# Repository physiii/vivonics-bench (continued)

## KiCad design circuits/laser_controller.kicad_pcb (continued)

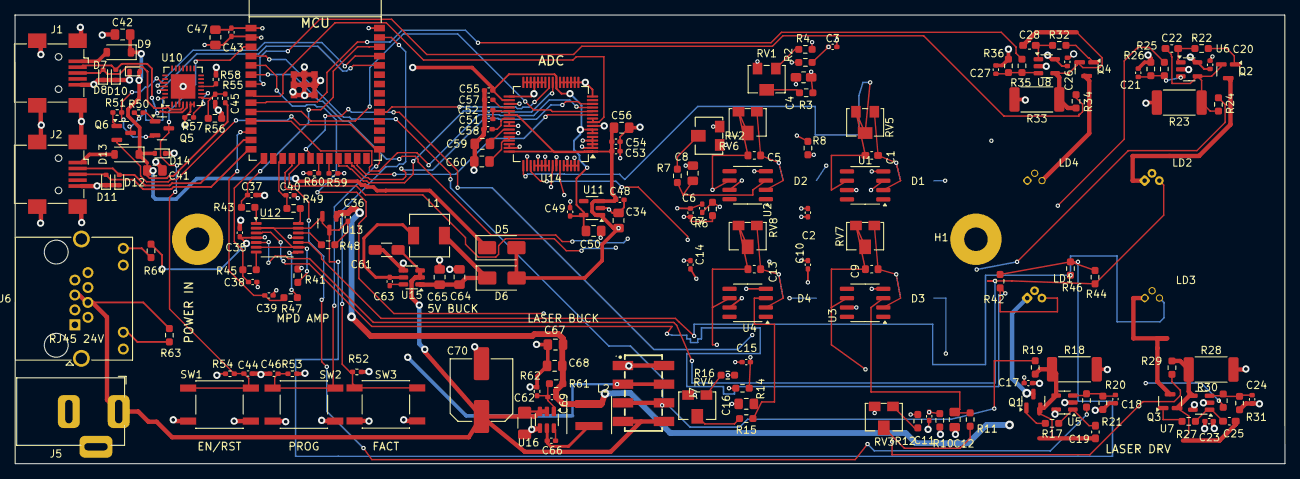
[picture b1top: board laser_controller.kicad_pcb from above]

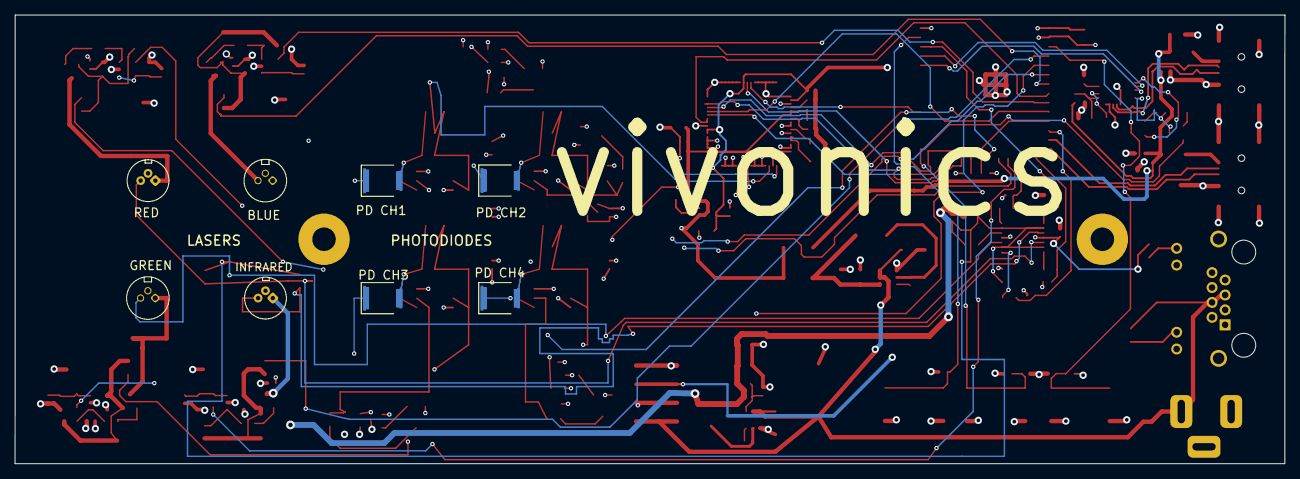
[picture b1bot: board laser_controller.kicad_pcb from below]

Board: 4 copper layers, 173.0 x 61.1 mm, 181 parts (8 on the bottom side), 110 nets.

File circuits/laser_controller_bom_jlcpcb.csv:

Comment,Designator,Footprint,LCSC
"240R MPD sense","R42,R44,R46,R48","Resistor_SMD:R_0603_1608Metric_Pad0.98x0.95mm_HandSolder","C103446"
"10pF C0G","C1,C5,C9,C13,C19,C22,C25,C28","Capacitor_SMD:C_0603_1608Metric_Pad1.08x0.95mm_HandSolder","C106245"
"RF 2M","RV5,RV6,RV7,RV8","Potentiometer_SMD:Potentiometer_Bourns_3224W_Vertical","C116323"
"SW_PUSH","SW1,SW2,SW3","Button_Switch_SMD:SW_SPST_PTS645","C127509"
"100pF FF","C69","Capacitor_SMD:C_0402_1005Metric_Pad0.74x0.62mm_HandSolder","C1546"
"10K","R59,R52,R58,R60,R53,R50,R51,R54","Resistor_SMD:R_0402_1005Metric_Pad0.72x0.64mm_HandSolder","C191123"
"C192300","J7","Open_Automation:PinHeader_2x04_P2.54mm_SMD_Vertical_C192300","C192300"
"24V DC IN","J5","Open_Automation:BarrelJack_OD5.5_ID2.5","C194407"
"OPA380AID","U1,U2,U3,U4","Package_SO:SOIC-8_3.9x4.9mm_P1.27mm","C201677"
"INA4180A1","U12","Package_SO:TSSOP-14_4.4x5mm_P0.65mm","C2057528"
"AP63205WU-7 5V BUCK","U15","Package_TO_SOT_SMD:TSOT-23-6","C2071056"
"AP63200WU-7 9.3V BUCK","U16","Package_TO_SOT_SMD:TSOT-23-6","C2071868"
"AO3400A","Q1,Q2,Q3,Q4","Package_TO_SOT_SMD:SOT-23","C20917"
"1.3k LIMIT","R21","Resistor_SMD:R_0603_1608Metric_Pad0.98x0.95mm_HandSolder","C22767"
"2.49k MPD bias","R41","Resistor_SMD:R_0603_1608Metric_Pad0.98x0.95mm_HandSolder","C22908"
"47.5K","R56","Resistor_SMD:R_0603_1608Metric_Pad0.98x0.95mm_HandSolder","C23061"
"4.7k LIMIT","R36","Resistor_SMD:R_0603_1608Metric_Pad0.98x0.95mm_HandSolder","C23162"
"750R LIMIT","R26","Resistor_SMD:R_0603_1608Metric_Pad0.98x0.95mm_HandSolder","C23241"
"SS14","D5,D6","Diode_SMD:D_SMA","C2480"
"SFH2201","D1,D2,D3,D4","OptoDevice:Osram_SFH2201","C2900216"
"1k","R2,R6,R10,R14,R17,R19,R22,R24,R27,R29,R32,R34","Resistor_SMD:R_0603_1608Metric_Pad0.98x0.95mm_HandSolder","C2907002"
"1k ADC","R43,R45,R47,R49","Resistor_SMD:R_0603_1608Metric_Pad0.98x0.95mm_HandSolder","C2907002"
"ESP32-S3-WROOM-1","U9","Espressif:ESP32-S3-WROOM-1","C2913199"
"22.1K","R55","Resistor_SMD:R_0402_1005Metric_Pad0.72x0.64mm_HandSolder","C2929993"
"22.1K FB","R62","Resistor_SMD:R_0402_1005Metric_Pad0.72x0.64mm_HandSolder","C2929993"
"237k FB","R61","Resistor_SMD:R_0603_1608Metric_Pad0.98x0.95mm_HandSolder","C2998117"
"10uF","C4,C8,C12,C16,C50","Capacitor_SMD:C_0805_2012Metric_Pad1.18x1.45mm_HandSolder","C318691"
"10uF +5V bulk","C34","Capacitor_SMD:C_0805_2012Metric_Pad1.18x1.45mm_HandSolder","C318691"
"10uF ADC AVCC","C56","Capacitor_SMD:C_0805_2012Metric_Pad1.18x1.45mm_HandSolder","C318691"
"10uF ADC REF","C59","Capacitor_SMD:C_0805_2012Metric_Pad1.18x1.45mm_HandSolder","C318691"
"10uF ADC REFCAP","C60","Capacitor_SMD:C_0805_2012Metric_Pad1.18x1.45mm_HandSolder","C318691"
"C_10uF","C41,C47,C42","Capacitor_SMD:C_0805_2012Metric_Pad1.18x1.45mm_HandSolder","C318691"
"CONN_RJ45","J6","Connector_RJ:RJ45_Amphenol_RJHSE538X","C386757"
"Q_L8550HQLT1G","Q6","Package_TO_SOT_SMD:SOT-23","C39282"
"TLV9001","U5,U6,U7,U8","Package_TO_SOT_SMD:SOT-23-5","C398363"
"4.7uH","L1","Open_Automation:L_5.4x5.3_H3","C408410"
"3k LIMIT","R31","Resistor_SMD:R_0603_1608Metric_Pad0.98x0.95mm_HandSolder","C4211"
"22uF 5V buck","C64,C65","Capacitor_SMD:C_0805_2012Metric_Pad1.18x1.45mm_HandSolder","C45783"
"22uF laser buck","C67,C68","Capacitor_SMD:C_0805_2012Metric_Pad1.18x1.45mm_HandSolder","C45783"
"USB_MINI_B","J2,J1","Connector_USB:USB_Mini-B_Wuerth_65100516121_Horizontal","C46391"
"Q_L8050QLT1G","Q5","Package_TO_SOT_SMD:SOT-23","C49581"
"AP2112K-3.3","U11","Package_TO_SOT_SMD:SOT-23-5","C51118"
"10R 2W","R18,R23,R28,R33","Resistor_SMD:R_2512_6332Metric_Pad1.40x3.35mm_HandSolder","C5123624"
"AD7606BSTZ-4","U14","Package_QFP:LQFP-64_10x10mm_P0.5mm","C51512"
"ESD_5V","D7,D14,D9,D11,D12,D8","Diode_SMD:D_SOD-523","C5199850"
"LM4040C50 5V","U13","Package_TO_SOT_SMD:SOT-23","C69316"
"1uF","C3,C7,C11,C15,C18,C21,C24,C27,C48,C46,C44,C45","Capacitor_SMD:C_0402_1005Metric_Pad0.74x0.62mm_HandSolder","C7472946"
"1uF ADC REGCAP","C57,C58","Capacitor_SMD:C_0402_1005Metric_Pad0.74x0.62mm_HandSolder","C7472946"
"VBIAS 10k","RV1,RV2,RV3,RV4","Potentiometer_SMD:Potentiometer_Bourns_3224W_Vertical","C81348"
"D_1N5819HW","D13,D10","Diode_SMD:D_SOD-123","C82544"
"100nF","C2,C6,C10,C14,C17,C20,C23,C26,C49,C35,C43","Capacitor_SMD:C_0402_1005Metric_Pad0.74x0.62mm_HandSolder","C83056"
"100nF ADC AVCC","C51,C52,C53,C54","Capacitor_SMD:C_0402_1005Metric_Pad0.74x0.62mm_HandSolder","C83056"
"100nF ADC VDRIVE","C55","Capacitor_SMD:C_0402_1005Metric_Pad0.74x0.62mm_HandSolder","C83056"
"100nF BST","C63,C66","Capacitor_SMD:C_0402_1005Metric_Pad0.74x0.62mm_HandSolder","C83056"
"100nF MPD ADC","C37,C38,C39,C40","Capacitor_SMD:C_0402_1005Metric_Pad0.74x0.62mm_HandSolder","C83056"
"100nF MPD bias","C36","Capacitor_SMD:C_0402_1005Metric_Pad0.74x0.62mm_HandSolder","C83056"
"10K","R63,R64","Resistor_SMD:R_0603_1608Metric_Pad0.98x0.95mm_HandSolder","C844918"
"10k","R4,R3,R8,R7,R12,R11,R16,R15,R20,R25,R30,R35","Resistor_SMD:R_0603_1608Metric_Pad0.98x0.95mm_HandSolder","C844918"
"1K","R57","Resistor_SMD:R_0402_1005Metric_Pad0.72x0.64mm_HandSolder","C852624"
"10uF 50V","C61,C62","Capacitor_SMD:C_1206_3216Metric_Pad1.33x1.80mm_HandSolder","C89632"
"CP2102N-Axx-xQFN28","U10","Package_DFN_QFN:QFN-28-1EP_5x5mm_P0.5mm_EP3.35x3.35mm","C964632"
"22uF 100V","C70","Capacitor_SMD:C_Elec_8x10.2","C970665"
"10uH","L2","Open_Automation:L_4x4","C98364"

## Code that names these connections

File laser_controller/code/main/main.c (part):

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    GPIO_PWM_GREEN = 12,
    GPIO_PWM_BLUE = 16,
    GPIO_ADC_CONVST = 15,
    GPIO_ADC_SCLK = 17,
    GPIO_ADC_CS = 18,
    GPIO_ADC_DOUTA = 21,
    GPIO_ADC_BUSY = 47,
    GPIO_ADC_RESET = 48,
};

static const char *TAG = "laser_controller";
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    LEDC_CHANNEL_3,
};
static const adc_channel_t TELEMETRY_CHANNELS[TELEMETRY_CHANNEL_COUNT] = {
    ADC_CHANNEL_3, /* GPIO4: ISENSE1 */
    ADC_CHANNEL_4, /* GPIO5: ISENSE2 */
    ADC_CHANNEL_5, /* GPIO6: ISENSE3 */
    ADC_CHANNEL_6, /* GPIO7: ISENSE4 */
    ADC_CHANNEL_1, /* GPIO2: MPD1 */
    ADC_CHANNEL_2, /* GPIO3: MPD2 */
    ADC_CHANNEL_7, /* GPIO8: MPD3 */
    ADC_CHANNEL_8, /* GPIO9: MPD4/spare */
};
static const gpio_num_t TELEMETRY_GPIOS[TELEMETRY_CHANNEL_COUNT] = {
    GPIO_NUM_4, /* ISENSE1 */
    GPIO_NUM_5, /* ISENSE2 */
    GPIO_NUM_6, /* ISENSE3 */
    GPIO_NUM_7, /* ISENSE4 */
    GPIO_NUM_2, /* MPD1 */
    GPIO_NUM_3, /* MPD2 */
    GPIO_NUM_8, /* MPD3 */
    GPIO_NUM_9, /* MPD4/spare */
};
static const char *const TELEMETRY_SIGNAL_NAMES[TELEMETRY_CHANNEL_COUNT] = {
    "ISENSE1",
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    force_all_lasers_off();

    const gpio_config_t adc_output_config = {
        .pin_bit_mask = (1ULL << GPIO_ADC_CONVST) | (1ULL << GPIO_ADC_RESET),
        .mode = GPIO_MODE_OUTPUT,
        .pull_up_en = GPIO_PULLUP_DISABLE,
        .pull_down_en = GPIO_PULLDOWN_ENABLE,
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        return error;
    }
    gpio_set_level(GPIO_ADC_CONVST, 0);
    gpio_set_level(GPIO_ADC_RESET, 0);

    const gpio_config_t busy_config = {
        .pin_bit_mask = 1ULL << GPIO_ADC_BUSY,
        .mode = GPIO_MODE_INPUT,
        .pull_up_en = GPIO_PULLUP_DISABLE,
        .pull_down_en = GPIO_PULLDOWN_DISABLE,
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    if (error != ESP_OK) {
        return error;
    }
    return gpio_isr_handler_add(GPIO_ADC_BUSY, adc_busy_rise_isr, NULL);
}

#if CONFIG_LC_ENABLE_LASER_PULSE_TEST
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    const spi_bus_config_t bus_config = {
        .mosi_io_num = -1,
        .miso_io_num = GPIO_ADC_DOUTA,
        .sclk_io_num = GPIO_ADC_SCLK,
        .quadwp_io_num = -1,
        .quadhd_io_num = -1,
        .max_transfer_sz = AD7606_DOUTA_FRAME_BYTES,
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        .dummy_bits = 0,
        .mode = 1,
        .clock_speed_hz = CONFIG_LC_AD7606_SCLK_HZ,
        .spics_io_num = GPIO_ADC_CS,
        .queue_size = 1,
        .flags = SPI_DEVICE_HALFDUPLEX | SPI_DEVICE_NO_DUMMY,
    };
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
static void reset_adc(void)
{
    const int busy_before = gpio_get_level(GPIO_ADC_BUSY);
    gpio_set_level(GPIO_ADC_RESET, 1);
    esp_rom_delay_us(10);
    const int busy_during_reset = gpio_get_level(GPIO_ADC_BUSY);
    gpio_set_level(GPIO_ADC_RESET, 0);
    esp_rom_delay_us(100);
    ESP_LOGI(
        TAG,
        "ADC_RESET_DIAG busy_before=%d busy_during=%d busy_after=%d",
        busy_before,
        busy_during_reset,
        gpio_get_level(GPIO_ADC_BUSY)
    );
}

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
static bool wait_for_adc_busy_rise(uint32_t timeout_us)
{
    if (adc_busy_rise_latched || gpio_get_level(GPIO_ADC_BUSY) == 1) {
        return true;
    }
    const int64_t deadline = esp_timer_get_time() + timeout_us;
    while (esp_timer_get_time() <= deadline) {
        if (adc_busy_rise_latched || gpio_get_level(GPIO_ADC_BUSY) == 1) {
            return true;
        }
    }
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{
    uint8_t raw[AD7606_DOUTA_FRAME_BYTES] = {0};

    const int busy_before = gpio_get_level(GPIO_ADC_BUSY);
    gpio_set_level(GPIO_ADC_CONVST, 0);
    esp_rom_delay_us(1);
    const int busy_while_convst_low = gpio_get_level(GPIO_ADC_BUSY);
    adc_busy_rise_latched = false;
    gpio_set_level(GPIO_ADC_CONVST, 1);
    const int busy_immediate = gpio_get_level(GPIO_ADC_BUSY);

    const int64_t rise_wait_started_us = esp_timer_get_time();
    if (busy_immediate != 1 &&
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            busy_while_convst_low,
            busy_immediate,
            adc_busy_rise_latched,
            gpio_get_level(GPIO_ADC_BUSY),
            esp_timer_get_time() - rise_wait_started_us
        );
        return LASER_FAULT_ADC_BUSY_RISE_TIMEOUT;
    }
    const int64_t busy_rise_us = esp_timer_get_time() - rise_wait_started_us;
    const int64_t fall_wait_started_us = esp_timer_get_time();
    if (!wait_for_gpio_level(GPIO_ADC_BUSY, 0, CONFIG_LC_AD7606_BUSY_TIMEOUT_US)) {
        ESP_LOGE(
            TAG,
            "ADC_BUSY_FALL_TIMEOUT busy_rise_us=%" PRId64 " busy_after=%d "
            "elapsed_us=%" PRId64,
            busy_rise_us,
            gpio_get_level(GPIO_ADC_BUSY),
            esp_timer_get_time() - fall_wait_started_us
        );
        return LASER_FAULT_ADC_BUSY_FALL_TIMEOUT;
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
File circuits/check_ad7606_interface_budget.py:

#!/usr/bin/env python3
"""AD7606-4 hardware strap and ESP32 serial-read budget check.

This is a firmware-interface contract for the current bench board. It proves
the schematic is wired for the intended AD7606-4 serial mode and that the
default firmware timing target has margin against the datasheet timing path.
It does not prove analog accuracy, final PCB layout, or working firmware.
"""
from __future__ import annotations

import os
import sys
from pathlib import Path

from check_laser_controller_netlist import parse_components, parse_netlist


ADC_REF = "U14"
ESP32_REF = "U9"
ADC_BITS = 16
ADC_CHANNELS = 4
DOUT_LINES = 2
INPUT_SPAN_V = 10.0  # +/-5 V range strap.
INPUT_LSB_UV = INPUT_SPAN_V / (2**ADC_BITS) * 1_000_000
DEFAULT_SPI_MHZ = 10.0
DEFAULT_TARGET_KSPS = 100.0
AD7606_4_NO_OS_CONV_US = 2.0
RESET_HIGH_MIN_NS = 50.0
RESET_TO_CONVST_MIN_NS = 25.0
CONVST_LOW_MIN_NS = 25.0
CONVST_HIGH_MIN_NS = 25.0
BUSY_TO_CS_MIN_NS = 0.0
READ_DURING_BUSY_T6_GUARD_NS = 25.0
DATASHEET_NO_OS_MAX_KSPS = 200.0
CONSERVATIVE_SPI_MAX_MHZ = 10.0


def env_float(name: str, default: float) -> float:
    raw = os.environ.get(name)
    if raw in (None, ""):
        return default
    return float(raw)


def node_set(nets: dict[str, list[tuple[str, str, str, str]]], net: str) -> set[tuple[str, str]]:
    return {(ref, pin) for ref, pin, _, _ in nets.get(net, [])}


def require_exact(
    errors: list[str],
    nets: dict[str, list[tuple[str, str, str, str]]],
    net: str,
    expected: set[tuple[str, str]],
) -> None:
    actual = node_set(nets, net)
    if actual != expected:
        errors.append(f"{net}: expected {sorted(expected)}, got {sorted(actual)}")


def require_contains(
    errors: list[str],
    nets: dict[str, list[tuple[str, str, str, str]]],
    net: str,
    expected_nodes: set[tuple[str, str]],
) -> None:
    actual = node_set(nets, net)
    missing = sorted(expected_nodes - actual)
    if missing:
        errors.append(f"{net}: missing expected node(s) {missing}; actual {sorted(actual)}")


def require_unconnected_pin(
    errors: list[str],
    nets: dict[str, list[tuple[str, str, str, str]]],
    ref: str,
    pin: str,
) -> None:
    connected = [
        net
        for net, nodes in sorted(nets.items())
        if any(node_ref == ref and node_pin == pin for node_ref, node_pin, _, _ in nodes)
    ]
    if connected:
        errors.append(f"{ref}.{pin}: expected intentional no-connect, got net(s) {connected}")


def main() -> int:
    netlist_path = Path(sys.argv[1]) if len(sys.argv) > 1 else Path("/tmp/lc.net")
    nets = parse_netlist(netlist_path)
    comps = parse_components(netlist_path)
    errors: list[str] = []

    comp = next((item for item in comps if item["ref"] == ADC_REF), None)
    if not comp:
        errors.append(f"{ADC_REF}: AD7606 component missing")
    elif comp["mpn"] != "AD7606BSTZ-4RL" or comp["footprint"] != "Package_QFP:LQFP-64_10x10mm_P0.5mm":
        errors.append(
            f"{ADC_REF}: expected AD7606BSTZ-4RL on LQFP-64 footprint, got "
            f"{comp['mpn']} / {comp['footprint']}"
        )

    require_exact(errors, nets, "VOUT1", {("C1", "2"), ("RV5", "2"), ("RV5", "3"), ("U1", "6"), (ADC_REF, "49")})
    require_exact(errors, nets, "VOUT2", {("C5", "2"), ("RV6", "2"), ("RV6", "3"), ("U2", "6"), (ADC_REF, "51")})
    require_exact(errors, nets, "VOUT3", {("C9", "2"), ("RV7", "2"), ("RV7", "3"), ("U3", "6"), (ADC_REF, "57")})
    require_exact(errors, nets, "VOUT4", {("C13", "2"), ("RV8", "2"), ("RV8", "3"), ("U4", "6"), (ADC_REF, "59")})

    require_exact(errors, nets, "CONVST", {(ADC_REF, "9"), (ADC_REF, "10"), (ESP32_REF, "8")})
    require_exact(errors, nets, "ADC_RESET", {(ADC_REF, "11"), (ESP32_REF, "25")})
    require_exact(errors, nets, "ADC_SCLK", {(ADC_REF, "12"), (ESP32_REF, "10")})
    require_exact(errors, nets, "ADC_CS", {(ADC_REF, "13"), (ESP32_REF, "11")})
    require_exact(errors, nets, "ADC_BUSY", {(ADC_REF, "14"), (ESP32_REF, "24")})
    require_exact(errors, nets, "ADC_MISO_A", {(ADC_REF, "24"), (ESP32_REF, "23")})
    require_exact(errors, nets, "ADC_MISO_B", {(ADC_REF, "25"), (ESP32_REF, "31")})

    require_contains(errors, nets, "+5V", {(ADC_REF, "1"), (ADC_REF, "37"), (ADC_REF, "38"), (ADC_REF, "48")})
    require_contains(errors, nets, "+3V3", {(ADC_REF, "6"), (ADC_REF, "7"), (ADC_REF, "23"), (ADC_REF, "34")})
    require_contains(
        errors,
        nets,
        "GND",
        {
            (ADC_REF, "3"),  # OS0
            (ADC_REF, "4"),  # OS1
            (ADC_REF, "5"),  # OS2
            (ADC_REF, "8"),  # RANGE: +/-5 V when low
            (ADC_REF, "16"), (ADC_REF, "17"), (ADC_REF, "18"), (ADC_REF, "19"),
            (ADC_REF, "20"), (ADC_REF, "21"), (ADC_REF, "22"),
            (ADC_REF, "27"), (ADC_REF, "28"), (ADC_REF, "29"), (ADC_REF, "30"),
            (ADC_REF, "31"), (ADC_REF, "32"), (ADC_REF, "33"),  # DB15/BYTE_SEL low: serial, not byte mode
            (ADC_REF, "35"), (ADC_REF, "40"), (ADC_REF, "41"),
            (ADC_REF, "43"), (ADC_REF, "46"),
            (ADC_REF, "47"), (ADC_REF, "50"), (ADC_REF, "52"), (ADC_REF, "53"),
            (ADC_REF, "54"), (ADC_REF, "55"), (ADC_REF, "56"), (ADC_REF, "58"),
            (ADC_REF, "60"), (ADC_REF, "61"), (ADC_REF, "62"), (ADC_REF, "63"), (ADC_REF, "64"),
        },
    )
    require_exact(errors, nets, "/POWER_IO/ADC_CREG1", {("C57", "1"), (ADC_REF, "36")})
    require_exact(errors, nets, "/POWER_IO/ADC_CREG2", {("C58", "1"), (ADC_REF, "39")})
    require_exact(errors, nets, "/POWER_IO/ADC_CREFIN", {("C59", "1"), (ADC_REF, "42")})
    require_exact(errors, nets, "/POWER_IO/ADC_REFCAP", {("C60", "1"), (ADC_REF, "44"), (ADC_REF, "45")})
    require_unconnected_pin(errors, nets, ADC_REF, "15")

    spi_mhz = env_float("LC_AD7606_SPI_MHZ", DEFAULT_SPI_MHZ)
    target_ksps = env_float("LC_AD7606_TARGET_KSPS", DEFAULT_TARGET_KSPS)
    bits_per_dout = ADC_BITS * ((ADC_CHANNELS + DOUT_LINES - 1) // DOUT_LINES)
    read_us = bits_per_dout / spi_mhz
    read_after_cycle_us = AD7606_4_NO_OS_CONV_US + read_us
    target_period_us = 1000.0 / target_ksps
    cycle_margin_us = target_period_us - read_after_cycle_us
    max_read_after_ksps = min(1000.0 / read_after_cycle_us, DATASHEET_NO_OS_MAX_KSPS)

    if spi_mhz > CONSERVATIVE_SPI_MAX_MHZ:
        errors.append(
            f"firmware SPI clock {spi_mhz:.2f} MHz exceeds conservative {CONSERVATIVE_SPI_MAX_MHZ:.2f} MHz policy "
            "for nominal 3.3 V VDRIVE; prove rail/timing margin before raising it"
        )
    if target_ksps > max_read_after_ksps:
        errors.append(
            f"target sample rate {target_ksps:.2f} kSPS exceeds read-after-conversion budget {max_read_after_ksps:.2f} kSPS"
        )
    if cycle_margin_us < 1.0:
        errors.append(f"target sample period leaves only {cycle_margin_us:.2f} us margin; keep at least 1 us firmware slack")

    if errors:
        print(f"FAIL AD7606 interface budget: {len(errors)} issue(s)")
        for error in errors:
            print(f"  - {error}")
        return 1

    print("PASS AD7606 interface budget")
    print("  hardware: AD7606BSTZ-4RL LQFP-64, AVCC=+5V, VDRIVE=+3V3, internal reference, serial mode")
    print("  straps: RANGE=0 (+/-5V), OS[2:0]=000 (no oversampling), STBY=1, REF_SELECT=1, DB15/BYTE_SEL=0")
    print("  ESP32: CONVST=GPIO15, SCLK=GPIO17, CS=GPIO18, BUSY=GPIO47, RESET=GPIO48, DOUTA=GPIO21, DOUTB=GPIO38")
    print(
        f"  read policy: {ADC_CHANNELS} channels, {DOUT_LINES} DOUT lines, {bits_per_dout:.0f} SCLK edges per DOUT line, "
        f"{spi_mhz:.2f}MHz SCLK -> {read_us:.2f}us read"
    )
    print(
        f"  timing budget: conversion={AD7606_4_NO_OS_CONV_US:.2f}us, read-after cycle={read_after_cycle_us:.2f}us, "
        f"target={target_ksps:.1f}kSPS period={target_period_us:.2f}us, margin={cycle_margin_us:.2f}us"
    )
    print(
        f"  firmware requirements: RESET high >= {RESET_HIGH_MIN_NS:.0f}ns, RESET-low to CONVST >= {RESET_TO_CONVST_MIN_NS:.0f}ns, "
        f"CONVST low/high >= {CONVST_LOW_MIN_NS:.0f}/{CONVST_HIGH_MIN_NS:.0f}ns, CS after BUSY fall >= {BUSY_TO_CS_MIN_NS:.0f}ns, "
        f"avoid reading on BUSY falling edge and keep >= {READ_DURING_BUSY_T6_GUARD_NS:.0f}ns guard if reading during conversion"
    )
    print(f"  scale: 16-bit twos-complement, +/-5V range, {INPUT_LSB_UV:.2f}uV/LSB")
    return 0


if __name__ == "__main__":
    raise SystemExit(main())

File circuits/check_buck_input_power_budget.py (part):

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    require_comp(failures, comps, ref_for("POWER_IO", "CBSTLASER"), mpn="0402B104K160CT", value_contains="100nF")

    for ref in [u15, u16]:
        require_net(failures, pin_nets, ref, "2", "VIN_24V")
        require_net(failures, pin_nets, ref, "3", "VIN_24V")
    require_net(failures, pin_nets, ref, "4", "GND")
    require_net(failures, pin_nets, u15, "1", "/POWER_IO/BUCK_5V")
    require_net(failures, pin_nets, u15, "5", "/POWER_IO/BUCK5_SW")
    require_net(failures, pin_nets, u15, "6", "/POWER_IO/BUCK5_BST")
    require_net(failures, pin_nets, u16, "1", "/POWER_IO/LASER_BUCK_FB")
    require_net(failures, pin_nets, u16, "5", "/POWER_IO/LASER_BUCK_SW")
    require_net(failures, pin_nets, u16, "6", "/POWER_IO/LASER_BUCK_BST")

    if not (9.2 <= actual_laser_vout_from_feedback() <= 9.5):
        failures.append(f"AP63200 feedback computes {actual_laser_vout_from_feedback():.2f}V, expected about 9.3V")
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
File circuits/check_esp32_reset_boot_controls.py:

#!/usr/bin/env python3
"""ESP32-S3 reset, boot, factory-button, and auto-programming topology check.

This gate covers the copied access-controller MCU control block around the
ESP32-S3 module and CP2102N: EN reset RC/button, GPIO0/BOOT programming
RC/button, GPIO1 factory button, CP2102N DTR/RTS transistor auto-reset network,
CP2102N RST/SUSPEND pulls, and the copied IO13/IO14 support pulls.
"""
from __future__ import annotations

import argparse
from pathlib import Path

from check_laser_controller_netlist import parse_components, parse_netlist


Node = tuple[str, str]


def node_set(nets: dict[str, list[tuple[str, str, str, str]]], net: str) -> set[Node]:
    return {(ref, pin) for ref, pin, _, _ in nets.get(net, [])}


def require_exact(
    errors: list[str],
    nets: dict[str, list[tuple[str, str, str, str]]],
    net: str,
    expected: set[Node],
) -> None:
    actual = node_set(nets, net)
    if actual != expected:
        errors.append(f"{net}: expected {sorted(expected)}, got {sorted(actual)}")


def require_members(
    errors: list[str],
    nets: dict[str, list[tuple[str, str, str, str]]],
    net: str,
    required: set[Node],
) -> None:
    actual = node_set(nets, net)
    missing = sorted(required - actual)
    if missing:
        errors.append(f"{net}: missing required node(s) {missing}; got {sorted(actual)}")


def require_comp(
    errors: list[str],
    comps: dict[str, dict[str, str]],
    ref: str,
    *,
    value: str,
    footprint: str,
    mpn: str,
    lcsc: str,
) -> None:
    actual = comps.get(ref)
    expected = {
        "value": value,
        "footprint": footprint,
        "mpn": mpn,
        "lcsc": lcsc,
    }
    if actual is None:
        errors.append(f"{ref}: component missing")
        return
    got = {key: actual.get(key, "") for key in expected}
    if got != expected:
        errors.append(f"{ref}: expected {expected}, got {got}")


def check_topology(netlist: Path) -> list[str]:
    errors: list[str] = []
    nets = parse_netlist(netlist)
    comps = {comp["ref"]: comp for comp in parse_components(netlist)}

    require_comp(
        errors,
        comps,
        "U9",
        value="ESP32-S3-WROOM-1",
        footprint="Espressif:ESP32-S3-WROOM-1",
        mpn="ESP32-S3-WROOM-1-N16",
        lcsc="C2913199",
    )
    require_comp(
        errors,
        comps,
        "U10",
        value="CP2102N-Axx-xQFN28",
        footprint="Package_DFN_QFN:QFN-28-1EP_5x5mm_P0.5mm_EP3.35x3.35mm",
        mpn="CP2102N-A02-GQFN28R",
        lcsc="C964632",
    )
    require_comp(
        errors,
        comps,
        "Q5",
        value="Q_L8050QLT1G",
        footprint="Package_TO_SOT_SMD:SOT-23",
        mpn="L8050QLT1G",
        lcsc="C49581",
    )
    require_comp(
        errors,
        comps,
        "Q6",
        value="Q_L8550HQLT1G",
        footprint="Package_TO_SOT_SMD:SOT-23",
        mpn="L8550HQLT1G",
        lcsc="C39282",
    )
    for ref in ("SW1", "SW2", "SW3"):
        require_comp(
            errors,
            comps,
            ref,
            value="SW_PUSH",
            footprint="Button_Switch_SMD:SW_SPST_PTS645",
            mpn="K2-1102SP-C4SC-04",
            lcsc="C127509",
        )
    for ref in ("R50", "R51", "R52", "R53", "R54", "R58", "R59", "R60"):
        require_comp(
            errors,
            comps,
            ref,
            value="10K",
            footprint="Resistor_SMD:R_0402_1005Metric_Pad0.72x0.64mm_HandSolder",
            mpn="ERJ2RKF1002X",
            lcsc="C191123",
        )
    require_comp(
        errors,
        comps,
        "R57",
        value="1K",
        footprint="Resistor_SMD:R_0402_1005Metric_Pad0.72x0.64mm_HandSolder",
        mpn="RT0402BRD071KL",
        lcsc="C852624",
    )
    for ref in ("C44", "C46"):
        require_comp(
            errors,
            comps,
            ref,
            value="1uF",
            footprint="Capacitor_SMD:C_0402_1005Metric_Pad0.74x0.62mm_HandSolder",
            mpn="HGC0402R5105K250NTEJ",
            lcsc="C7472946",
        )

    require_exact(errors, nets, "/MCU_ESP32-S3/EN", {("U9", "3"), ("R54", "2"), ("C44", "1"), ("SW1", "1"), ("Q5", "3")})
    require_exact(errors, nets, "/MCU_ESP32-S3/PROG", {("U9", "27"), ("R53", "2"), ("C46", "1"), ("SW2", "1"), ("Q6", "2")})
    require_exact(errors, nets, "/MCU_ESP32-S3/FACT", {("U9", "39"), ("R52", "2"), ("SW3", "1")})

    require_exact(errors, nets, "/MCU_ESP32-S3/DTR", {("U10", "28"), ("R50", "1"), ("Q6", "3")})
    require_exact(errors, nets, "/MCU_ESP32-S3/RTS", {("U10", "24"), ("R51", "1"), ("Q5", "2")})
    require_exact(errors, nets, "/MCU_ESP32-S3/AUTO_EN_BASE", {("Q5", "1"), ("R50", "2")})
    require_exact(errors, nets, "/MCU_ESP32-S3/AUTO_BOOT_BASE", {("Q6", "1"), ("R51", "2")})

    require_exact(errors, nets, "/MCU_ESP32-S3/CP2102_RST", {("U10", "9"), ("R57", "2")})
    require_exact(errors, nets, "/MCU_ESP32-S3/CP2102_SUSPEND_N", {("U10", "11"), ("R58", "1")})
    require_exact(errors, nets, "/MCU_ESP32-S3/IO13", {("U9", "21"), ("R60", "1")})
    require_exact(errors, nets, "/MCU_ESP32-S3/IO14", {("U9", "22"), ("R59", "2")})

    require_members(
        errors,
        nets,
        "+3V3",
        {
            ("U9", "2"),
            ("U10", "6"),
            ("U10", "7"),
            ("R52", "1"),
            ("R53", "1"),
            ("R54", "1"),
            ("R57", "1"),
            ("R59", "1"),
            ("R60", "2"),
        },
    )
    require_members(
        errors,
        nets,
        "GND",
        {
            ("C44", "2"),
            ("C46", "2"),
            ("R58", "2"),
            ("SW1", "2"),
            ("SW2", "2"),
            ("SW3", "2"),
            ("U9", "1"),
            ("U9", "40"),
            ("U9", "41"),
            ("U10", "3"),
            ("U10", "29"),
        },
    )
    return errors


def main() -> int:
    parser = argparse.ArgumentParser(description=__doc__)
    parser.add_argument("--netlist", type=Path, default=Path("/tmp/lc.net"))
    args = parser.parse_args()

    errors = check_topology(args.netlist)
    if errors:
        print("FAIL ESP32 reset/boot controls")
        for error in errors:
            print(f"  - {error}")
        return 1

    print(
        "PASS ESP32 reset/boot controls: EN 10k/1uF/reset, "
        "GPIO0 BOOT 10k/1uF/PROG, GPIO1 FACT, CP2102N DTR/RTS "
        "auto-reset transistors, RST/SUSPEND pulls, and IO13/IO14 pulls "
        "match the exported schematic"
    )
    return 0


if __name__ == "__main__":
    raise SystemExit(main())

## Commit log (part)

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2026-05-08 Update Vivonics roadmap and bench planning
2026-05-08 Prepare standalone Pi bench repo
2026-05-08 Use virtualenv for Pi bench install
2026-05-08 Exclude submodule git marker during deploy
2026-05-08 Use desktop display before dummy projector fallback
2026-05-08 Open projector in measurement worker
2026-05-08 Use absolute i2cdetect path in Pi docs
2026-05-20 feat(jig): add bench jig assets
2026-05-20 feat(jig): add 3mf bench jig package
2026-05-22 feat(bench): add laser GPIO control, multiply demo, and service upgrades
    Add laser_gpio.py for direct PWM control of red/green lasers and
    multiply_demo.py for bR analog multiplication experiments. Upgrade
    bench_service.py with direct picamera2 capture at 148fps, experiment
    orchestration, and green self-modulation measurement. Update jig model
    and deployment docs.
2026-05-25 feat(bench): add reactor jig and pigpio laser control
2026-05-25 feat(bench): add raw pulse measurement mode
2026-05-25 fix(bench): fall back to rpi gpio laser pwm
2026-05-25 fix(bench): restore video mode after raw runs
2026-05-27 feat(bench): add AD7606 reactor readout support
2026-05-31 feat(circuits): reactor TIA OPA380 schematic + JLCPCB BOM + datasheets
    2x OPA380AID single-channel TIA front-end to recover the ~1% red M-state
    modulation the passive 100k load could not resolve. KiCad v7 schematic with
    a generator that keeps the schematic and JLCPCB BOM in sync, plus the
    OPA380/BPW34 datasheets.
2026-05-31 chore(jig): update jig model + add electro-photonic coupler 3mf/stl
2026-06-01 refactor(circuits): redraw reactor TIA schematic with signal flow, power symbols, concise BOM
    Rewrote gen_reactor_tia_sch.py to emit a hand-laid-out, left-to-right schematic (D1 -> U1 TIA with R_f||C_f feedback -> Sallen-Key U2 -> J1), real wires, +5V/GND power symbols, and net labels. Regene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
2026-06-01 feat(circuits): dual-channel reactor TIA (1 OPA380 per channel)
    Retire the single-channel 2-stage TIA (TIA + Sallen-Key). The board is now two independent channels, one OPA380AID TIA each (BPW34 -> TIA -> V_CHn), sharing one VBIAS divider. Anti-alias rides on the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
    Generator is the source of truth (parametric, N-channel). 14 SMT / 18 total, 8 nets, netlist-validated. README rewritten to per-channel topology + new BOM.
2026-06-03 chore(models): reorganize jig CAD into models/, add test-tube holders
    Move jig designs into models/jig/ and add models (test-tube holders + downloaded 12mm base). Keep Blender sources (*.blend); large regenerable exports (Untitled.stl/3mf, sliced gcode) are NOT stored 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
2026-06-05 chore(models): update 24-tube test-tube holder .blend source
2026-06-11 feat(bench): add reactor optics control updates
2026-06-17 feat: fast AD7606 mmap reader (12.5 kHz, 32× speedup) + M-state decay test
    - ad7606_fast.py: direct /dev/gpiomem mmap, 80 μs/frame vs 2,500 μs
    - fast_mstate_decay.py: on-Pi retention test with mmap ADC + mmap laser control
    Sustained 10.9 kHz, 5,400+ frames per run, SEM 0.41 counts
2026-06-17 feat: precision M-state decay tests — HTTP+PWM, green selfmod, red probe with 3x filter
    - fast_decay_http_laser.py: HTTP PWM laser control + mmap ADC
    - fast_green_selfmod.py: green self-modulation with mmap GPIO
    - fast_red_decay_precise.py: dual-laser mmap, red probe after green write
2026-06-17 feat: IR probe weight sweep (null result at 780nm)
2026-06-17 feat: red weight bit precision — fast mmap, within-capture differential
    7 write durations × 8 reps, 200ms continuous capture per trial
    Early vs late frames compared within same capture (no inter-read drift)
    Result: M-state signal confirmed at 0.096% ΔT, but trial-to-trial drift
    (21 ct) exceeds multi-level signal range (8 ct). Binary only at 650nm.
    570nm probe needed for multi-bit weights.
2026-06-26 feat: add laser controller board and bench updates
2026-06-26 fix: report split rail groups in release gate
2026-06-26 chore(circuits): update laser controller release artifacts
2026-06-28 fix(circuits): import mcu sheet and laser footprints
2026-06-28 fix(circuits): restore placed laser controller pcb
2026-06-28 save laser controller schematic and layout state
2026-06-29 fix pcb update footprint identity
2026-06-29 save current laser controller recovery state
2026-06-29 group laser controller footprints outside board
2026-06-29 save user laser controller placement
2026-06-29 save latest laser controller placement
2026-06-29 clone TIA placement for PD channels
2026-06-29 clone laser placement for laser channels
2026-06-29 clean up power io schematic presentation
2026-06-30 save latest laser controller pcb placement
2026-06-30 add onboard laser controller supplies
2026-06-30 align laser controller power docs and checks
2026-06-30 Update laser controller power input to 24V
2026-06-30 Regenerate 24V power IO schematic
2026-06-30 Save laser controller RJ45 work
2026-06-30 Use access-controller RJ45 in power IO
2026-06-30 Spread out power IO schematic
2026-06-30 Save current laser controller backup state
